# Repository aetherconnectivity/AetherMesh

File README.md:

# AetherMesh
Design resources for the Sub-GHz AetherMesh modules

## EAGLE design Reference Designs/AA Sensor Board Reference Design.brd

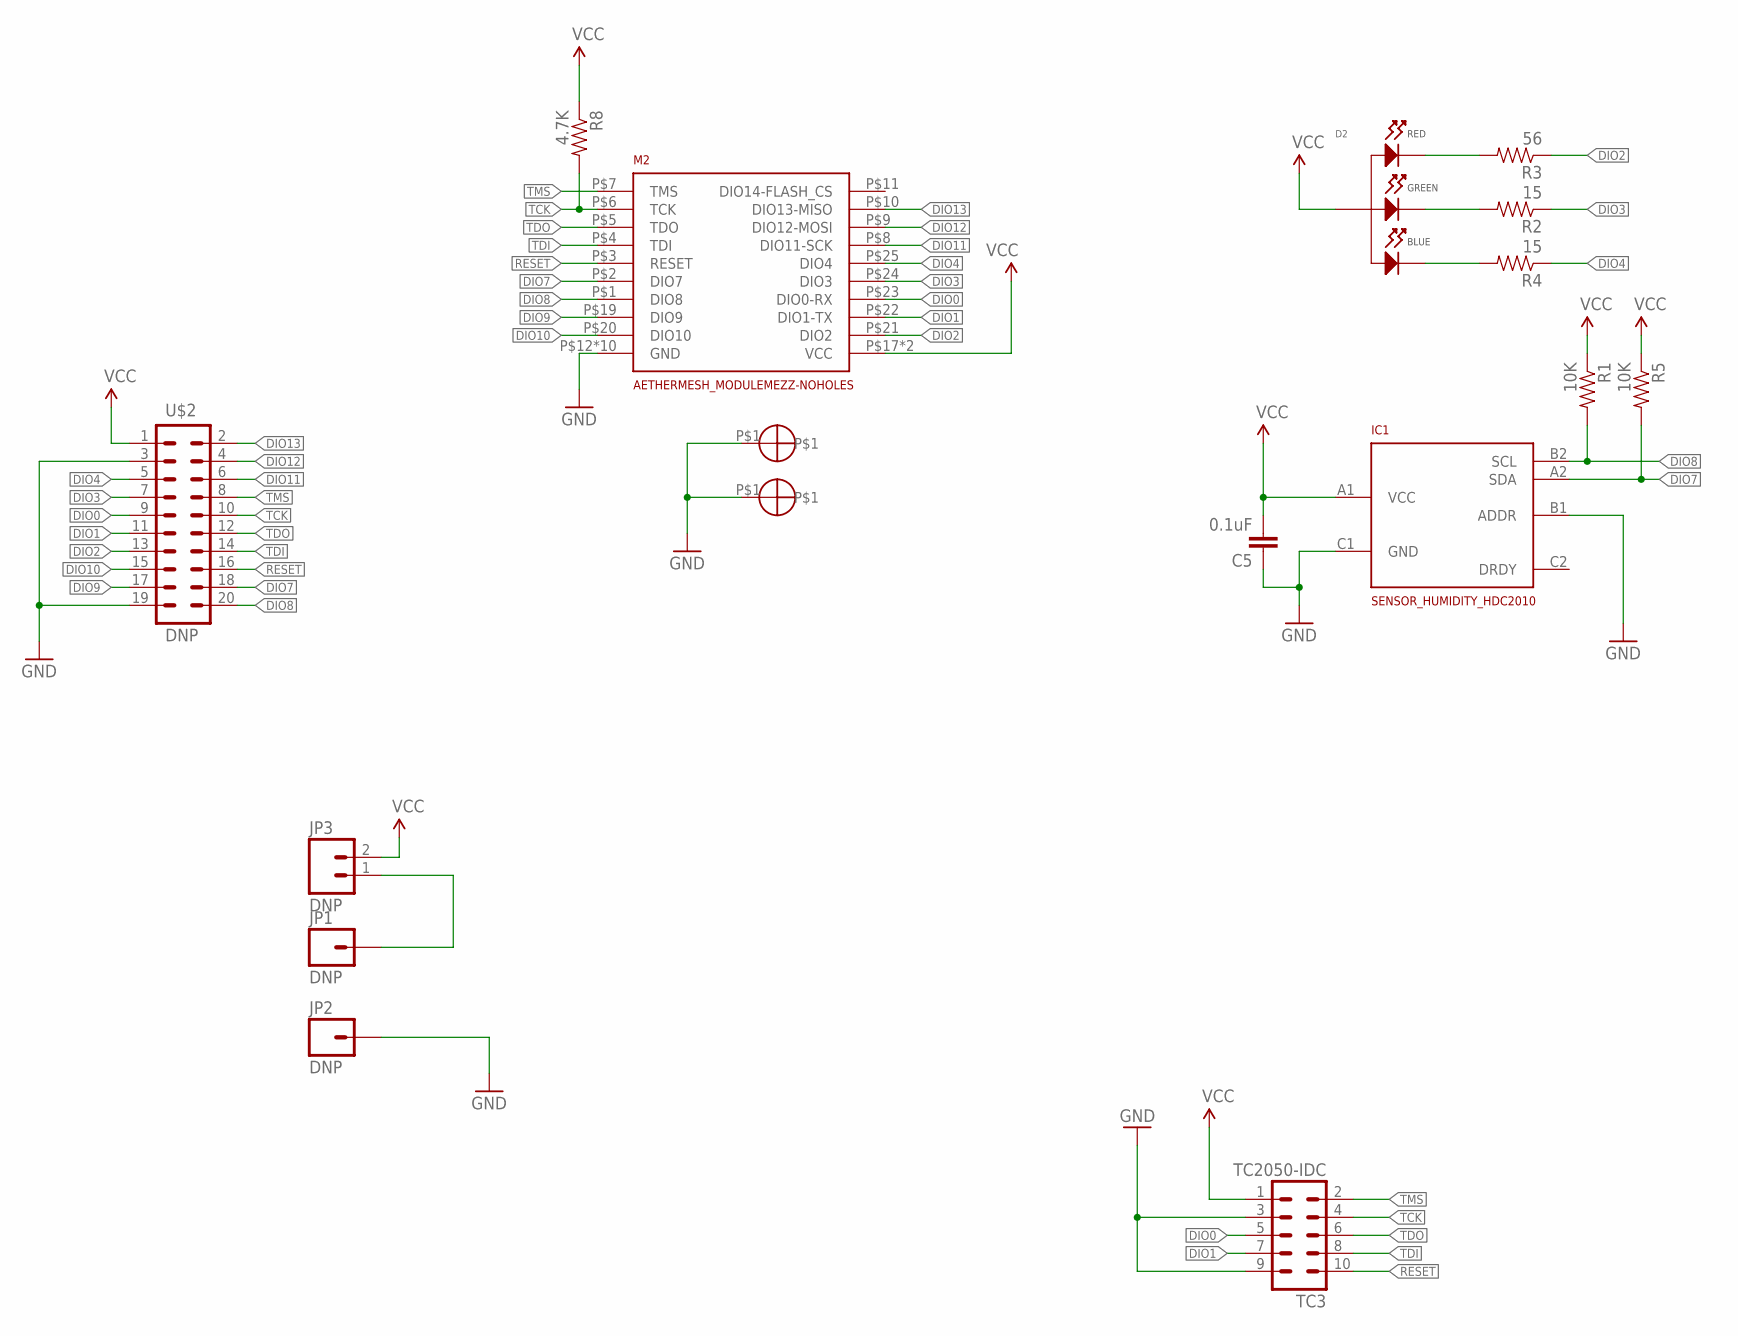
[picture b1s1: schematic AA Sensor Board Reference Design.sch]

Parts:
C5: 0.1uF; C0402; MFG# MF-CAP-0402-0.1uF
D2: LED_RGB_CA_PLCC4; PLCC4; MFG# MF-LED-3228-RGB
IC1: SENSOR_HUMIDITY_HDC2010; HDC2010
JP1, JP2: DNP; 1X01_3.5X.75_BATT_SLOT
JP3: DNP; 1X02_LOCK
M2: AETHERMESH_MODULEMEZZ-NOHOLES; AETHERMESH_MEZZ_MOUNT_NOHOLES
R1, R5: 10K; R0402; MFG# MF-RES-0402-10K
R2, R4: 15; R0402; MFG# RC0402JR-0715RL
R3: 56; R0402; MFG# RC0402JR-0756RL
R8: 4.7K; R0402; MFG# MF-RES-0402-4.7K
S3, S4: STANDOFFWURTH; STANDOFF_WURTH_9774040243R; MFG# 9774040243R
TC3: TC2050-IDC
U$2: DNP; 2X10_LOCK

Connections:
B2: D2.P$2 (CATHODE_RED), R3.P$2 (2)
DIO0: M2.P$23 (DIO0-RX), TC3.5, U$2.9
DIO1: M2.P$22 (DIO1-TX), TC3.7, U$2.11
DIO2: M2.P$21 (DIO2), R3.P$1 (1), U$2.13
DIO3: M2.P$24 (DIO3), R2.P$1 (1), U$2.7
DIO4: M2.P$25 (DIO4), R4.P$1 (1), U$2.5
DIO7: IC1.A2 (SDA), M2.P$2 (DIO7), R5.P$2 (2), U$2.18
DIO8: IC1.B2 (SCL), M2.P$1 (DIO8), R1.P$2 (2), U$2.20
DIO9: M2.P$19 (DIO9), U$2.17
DIO10: M2.P$20 (DIO10), U$2.15
DIO11: M2.P$8 (DIO11-SCK), U$2.6
DIO12: M2.P$9 (DIO12-MOSI), U$2.4
DIO13: M2.P$10 (DIO13-MISO), U$2.2
G2: D2.P$3 (CATHODE_GREEN), R2.P$2 (2)
GND: C5.P$1 (1), IC1.B1 (ADDR), IC1.C1 (GND), JP2.P$1, M2.P$12 (GND), M2.P$13 (GND), M2.P$14 (GND), M2.P$15 (GND), M2.P$16 (GND), M2.P$26 (GND), M2.P$27 (GND), M2.P$28 (GND), M2.P$29 (GND), M2.P$30 (GND), S3.P$1, S4.P$1, TC3.3, TC3.9, U$2.3, U$2.19
unnamed: JP1.P$1, JP3.1
R2: D2.P$4 (CATHODE_BLUE), R4.P$2 (2)
RESET: M2.P$3 (RESET), TC3.10, U$2.16
TCK: M2.P$6 (TCK), R8.P$2 (2), TC3.4, U$2.10
TDI: M2.P$4 (TDI), TC3.8, U$2.14
TDO: M2.P$5 (TDO), TC3.6, U$2.12
TMS: M2.P$7 (TMS), TC3.2, U$2.8
VCC: C5.P$2 (2), D2.P$1 (ANODE), IC1.A1 (VCC), JP3.2, M2.P$17 (VCC), M2.P$18 (VCC), R1.P$1 (1), R5.P$1 (1), R8.P$1 (1), TC3.1, U$2.1

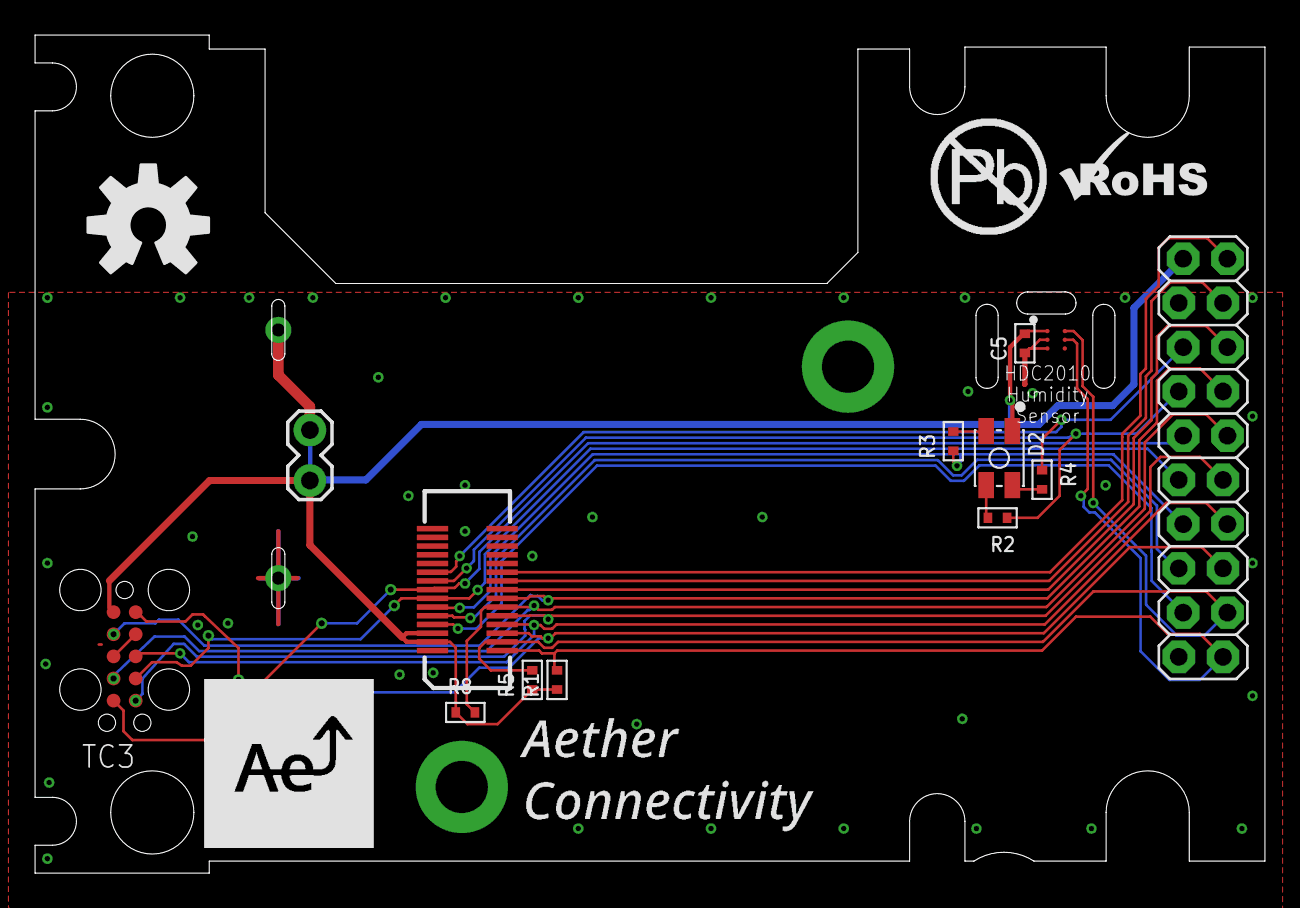
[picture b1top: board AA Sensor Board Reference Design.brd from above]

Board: 4 copper layers, 70.6 x 48.1 mm, 18 parts (0 on the bottom side), 23 nets.

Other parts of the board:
U$3: OSHW-LOGO-L

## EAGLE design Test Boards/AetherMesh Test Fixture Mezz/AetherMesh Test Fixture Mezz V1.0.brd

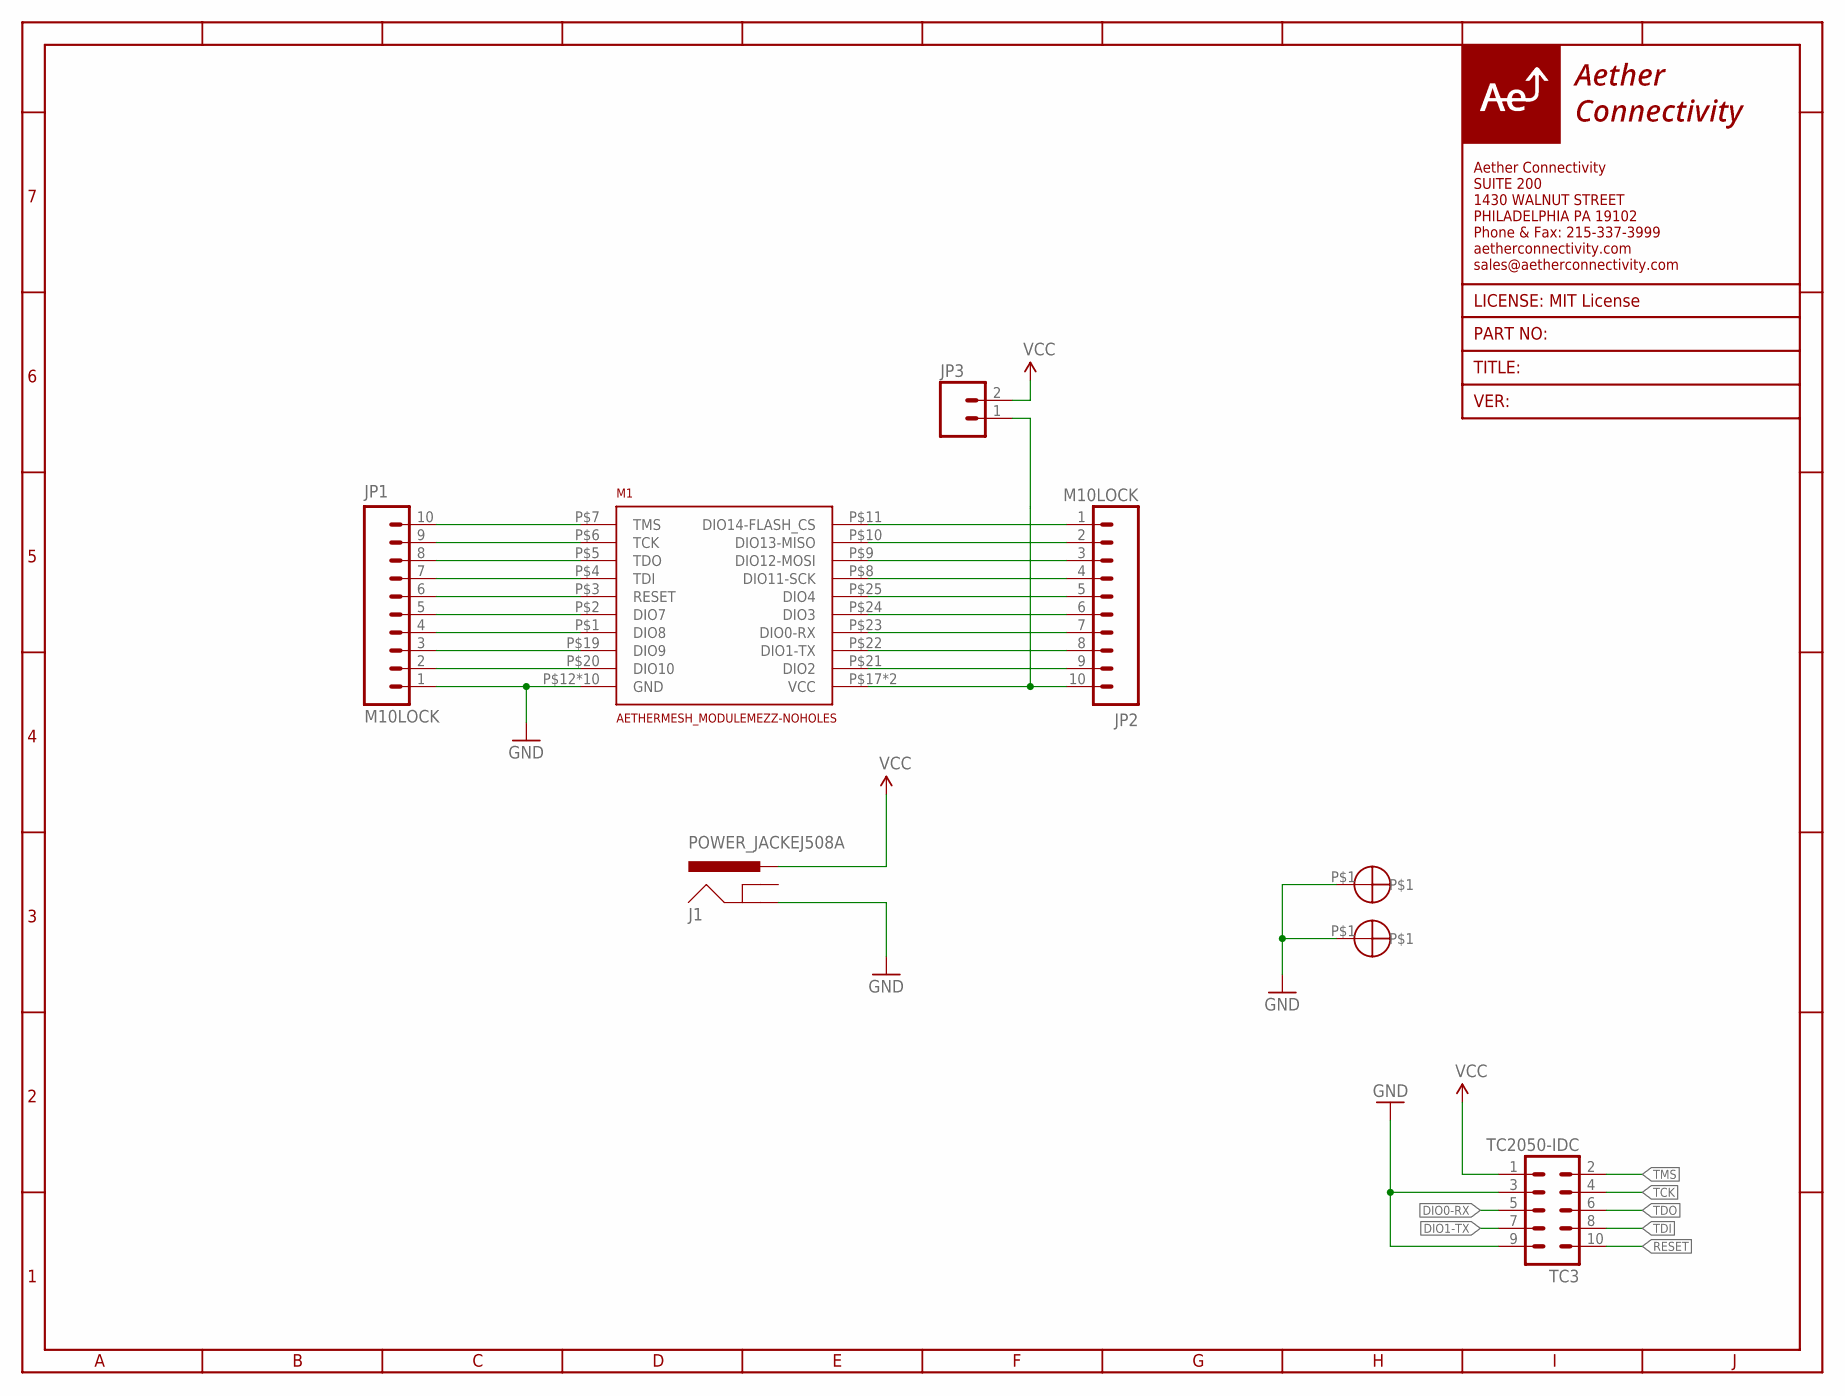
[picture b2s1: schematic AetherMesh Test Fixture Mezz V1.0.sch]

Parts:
J1: POWER_JACKEJ508A; DC_JACK_EJ508A
JP1, JP2: M10LOCK; 1X10_LOCK
JP3: M02LOCK; 1X02_LOCK
M1: AETHERMESH_MODULEMEZZ-NOHOLES; AETHERMESH_MEZZ_MOUNT_NOHOLES
S1, S2: STANDOFFWURTH; STANDOFF_WURTH_9774040243R; MFG# 9774040243R
TC3: TC2050-IDC

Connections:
BUTTON: JP1.2, M1.P$20 (DIO10)
CS: JP1.5, M1.P$2 (DIO7)
DIO0-RX: JP2.7, M1.P$23 (DIO0-RX), TC3.5
DIO1-TX: JP2.8, M1.P$22 (DIO1-TX), TC3.7
DIO2: JP2.9, M1.P$21 (DIO2)
DIO3: JP2.6, M1.P$24 (DIO3)
DIO4: JP2.5, M1.P$25 (DIO4)
ENC_RESET: JP1.4, M1.P$1 (DIO8)
GND: J1.1 (GND), JP1.1, M1.P$12 (GND), M1.P$13 (GND), M1.P$14 (GND), M1.P$15 (GND), M1.P$16 (GND), M1.P$26 (GND), M1.P$27 (GND), M1.P$28 (GND), M1.P$29 (GND), M1.P$30 (GND), S1.P$1, S2.P$1, TC3.3, TC3.9
INT: JP1.3, M1.P$19 (DIO9)
MISO: JP2.2, M1.P$10 (DIO13-MISO)
MOSI: JP2.3, M1.P$9 (DIO12-MOSI)
unnamed: JP2.1, M1.P$11 (DIO14-FLASH_CS)
unnamed: JP2.10, JP3.1, M1.P$17 (VCC), M1.P$18 (VCC)
RESET: JP1.6, M1.P$3 (RESET), TC3.10
SCK: JP2.4, M1.P$8 (DIO11-SCK)
TCK: JP1.9, M1.P$6 (TCK), TC3.4
TDI: JP1.7, M1.P$4 (TDI), TC3.8
TDO: JP1.8, M1.P$5 (TDO), TC3.6
TMS: JP1.10, M1.P$7 (TMS), TC3.2
VCC: J1.3 (PWR), JP3.2, TC3.1

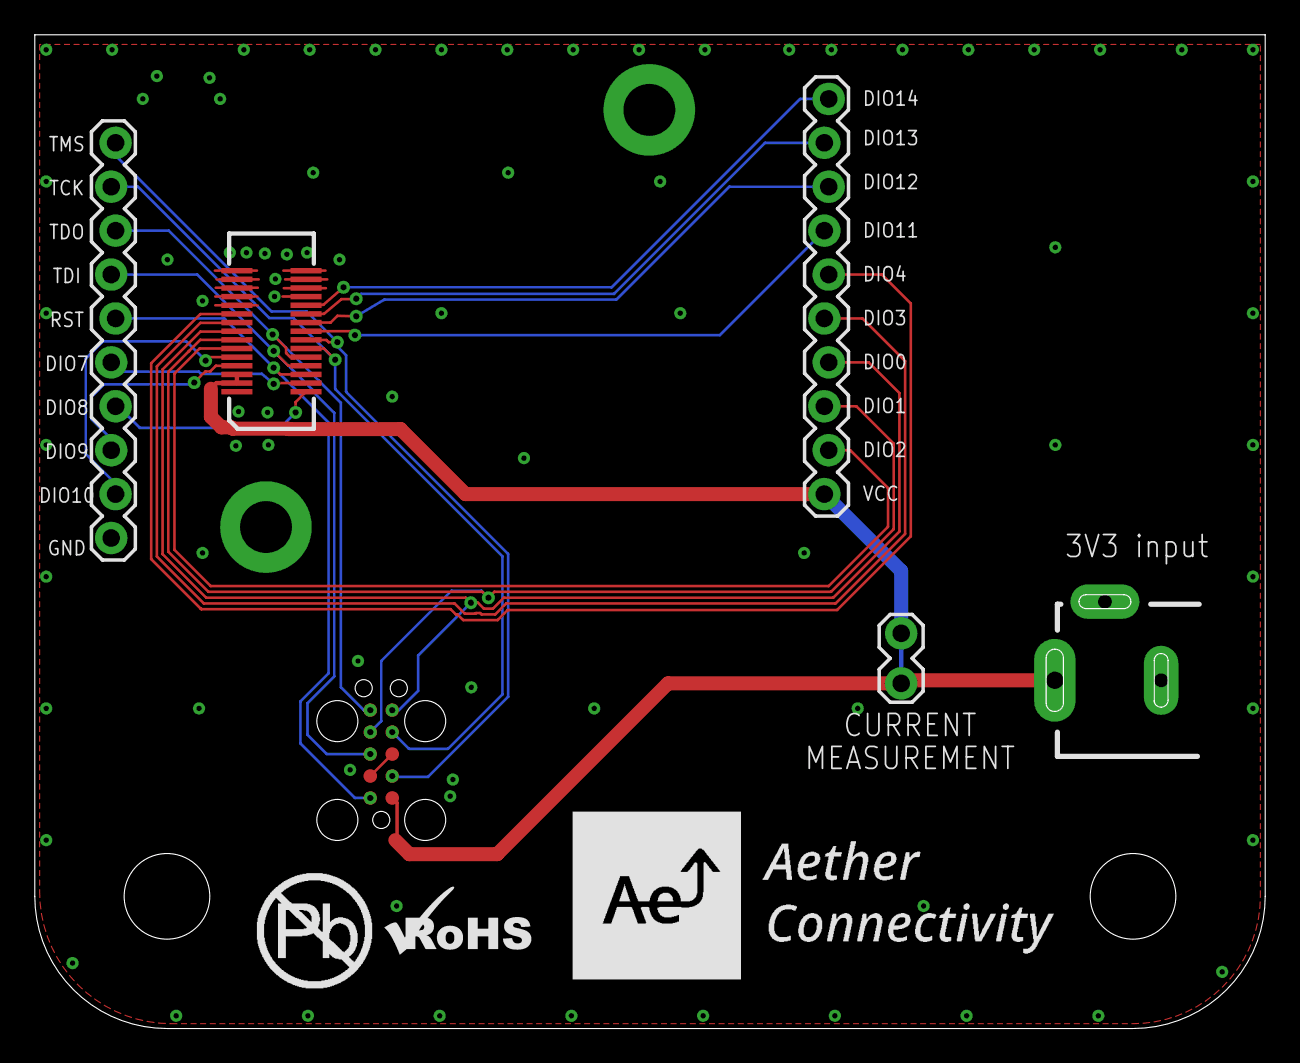
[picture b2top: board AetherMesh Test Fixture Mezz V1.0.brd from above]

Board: 2 copper layers, 71.2 x 57.5 mm, 8 parts (0 on the bottom side), 21 nets.

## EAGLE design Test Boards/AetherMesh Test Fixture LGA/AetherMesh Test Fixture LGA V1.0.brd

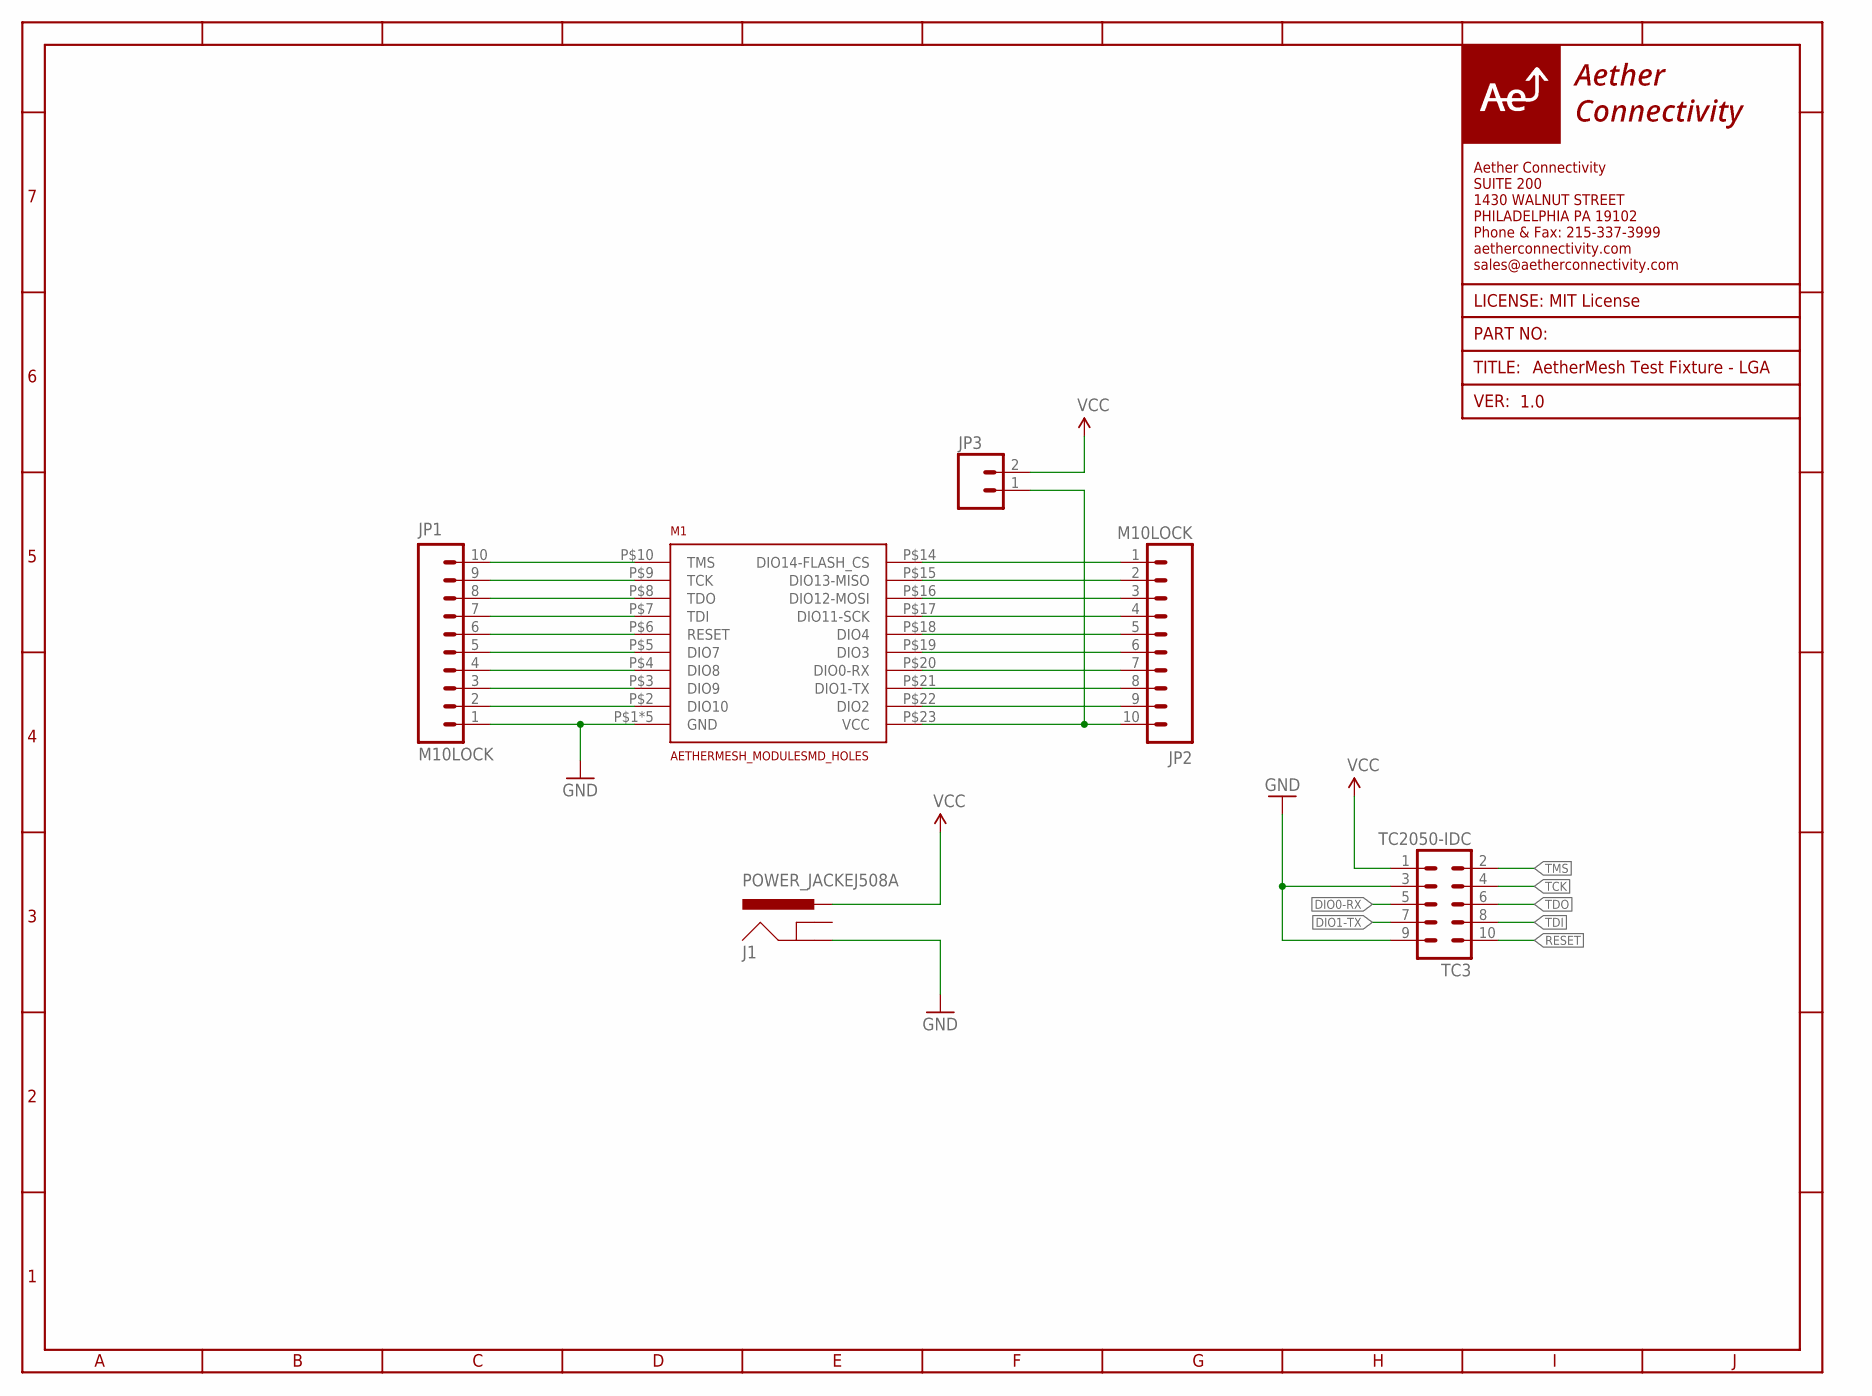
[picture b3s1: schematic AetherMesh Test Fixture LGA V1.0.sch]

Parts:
J1: POWER_JACKEJ508A; DC_JACK_EJ508A
JP1, JP2: M10LOCK; 1X10_LOCK
JP3: M02LOCK; 1X02_LOCK
M1: AETHERMESH_MODULESMD_HOLES; AETHERMESH_SMD_MOUNT_HOLES
TC3: TC2050-IDC

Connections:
BUTTON: JP1.2, M1.P$2 (DIO10)
CS: JP1.5, M1.P$5 (DIO7)
DIO0-RX: JP2.7, M1.P$20 (DIO0-RX), TC3.5
DIO1-TX: JP2.8, M1.P$21 (DIO1-TX), TC3.7
DIO2: JP2.9, M1.P$22 (DIO2)
DIO3: JP2.6, M1.P$19 (DIO3)
DIO4: JP2.5, M1.P$18 (DIO4)
ENC_RESET: JP1.4, M1.P$4 (DIO8)
GND: J1.1 (GND), JP1.1, M1.P$1 (GND), M1.P$11 (GND), M1.P$12 (GND), M1.P$13 (GND), M1.P$24 (GND), TC3.3, TC3.9
INT: JP1.3, M1.P$3 (DIO9)
MISO: JP2.2, M1.P$15 (DIO13-MISO)
MOSI: JP2.3, M1.P$16 (DIO12-MOSI)
unnamed: JP2.1, M1.P$14 (DIO14-FLASH_CS)
unnamed: JP2.10, JP3.1, M1.P$23 (VCC)
RESET: JP1.6, M1.P$6 (RESET), TC3.10
SCK: JP2.4, M1.P$17 (DIO11-SCK)
TCK: JP1.9, M1.P$9 (TCK), TC3.4
TDI: JP1.7, M1.P$7 (TDI), TC3.8
TDO: JP1.8, M1.P$8 (TDO), TC3.6
TMS: JP1.10, M1.P$10 (TMS), TC3.2
VCC: J1.3 (PWR), JP3.2, TC3.1

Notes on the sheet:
1.0
AetherMesh Test Fixture - LGA

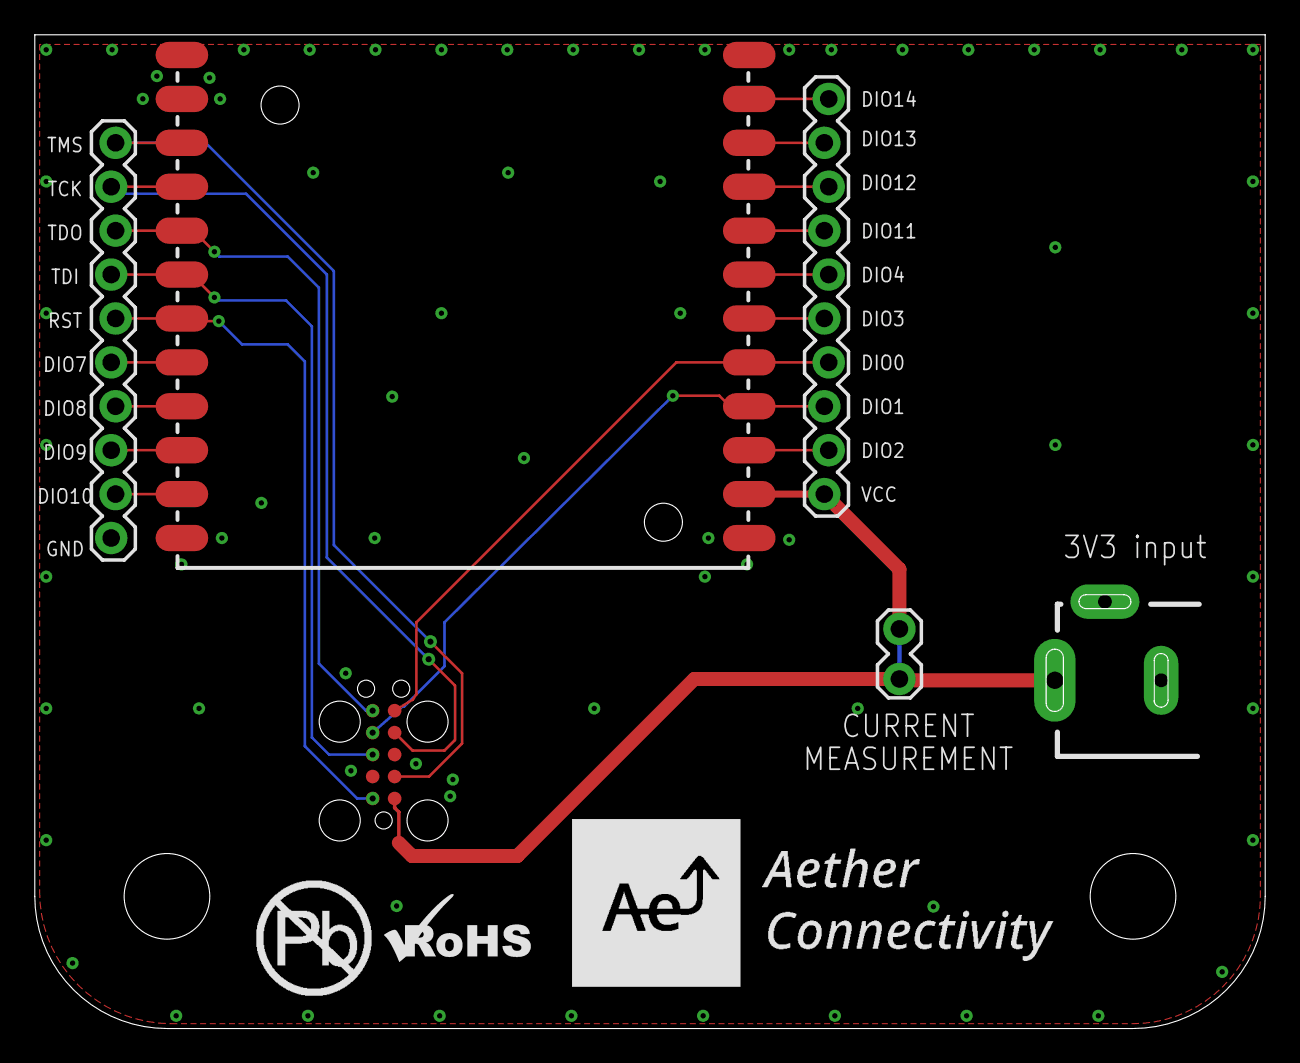
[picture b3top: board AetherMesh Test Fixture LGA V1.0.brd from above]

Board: 2 copper layers, 71.2 x 57.5 mm, 6 parts (0 on the bottom side), 21 nets.

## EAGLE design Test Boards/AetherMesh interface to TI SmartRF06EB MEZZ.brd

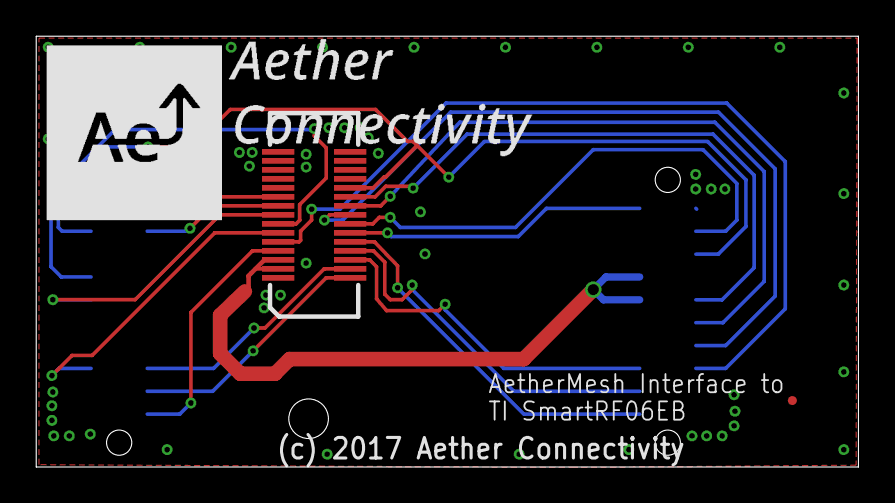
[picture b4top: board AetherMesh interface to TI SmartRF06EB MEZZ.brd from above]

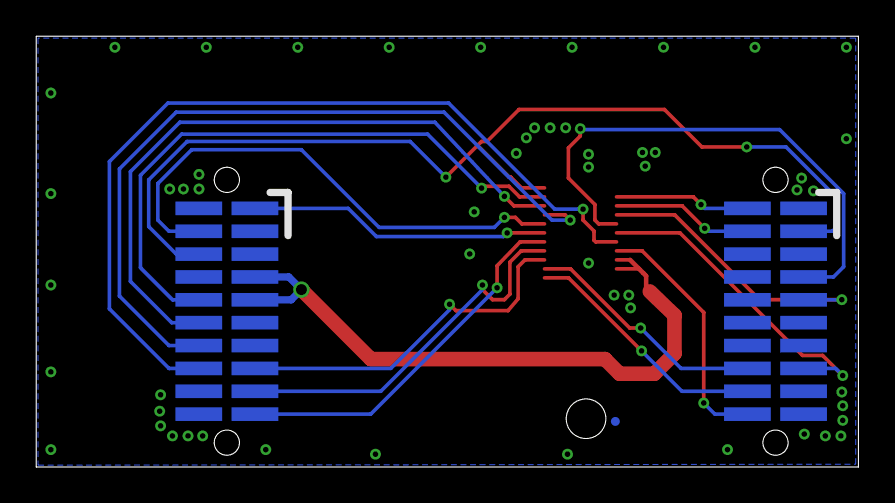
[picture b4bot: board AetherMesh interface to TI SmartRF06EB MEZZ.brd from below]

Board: 4 copper layers, 45.7 x 23.9 mm, 5 parts (3 on the bottom side), 20 nets.

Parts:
FID1, FID2: FIDUCIAL_0.5MM
M1: AETHERMESH_MODULEMEZZ-NOHOLES; AETHERMESH_MEZZ_MOUNT_NOHOLES
P1, P2: M2X10SFM; 2X10_SFM-110-02-S-D-A-K-TR

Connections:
DIO0-RX: M1.P$23, P1.9
DIO1-TX: M1.P$22, P1.7
DIO2: M1.P$21, P1.15
DIO3: M1.P$24, P1.4
DIO4: M1.P$25, P1.2
DIO7: M1.P$2, P1.16
DIO8: M1.P$1, P1.18
DIO9: M1.P$19, P1.20
DIO10: M1.P$20, P2.16
FLASH_CS: M1.P$11, P1.3, P2.6
GND: M1.P$12, M1.P$13, M1.P$14, M1.P$15, M1.P$16, M1.P$26, M1.P$27, M1.P$28, M1.P$29, M1.P$30, P1.1, P1.19, P2.2, P2.20
MISO: M1.P$10, P2.10
MOSI: M1.P$9, P2.12
RESET_N: M1.P$3, P2.15
SCK: M1.P$8, P2.14
TCK: M1.P$6, P2.1
TDI: M1.P$4, P2.17
TDO: M1.P$5, P2.19
TMS: M1.P$7, P2.4
VCC: M1.P$17, M1.P$18, P2.7, P2.9

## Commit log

2017-08-22 Initial commit of AetherMesh test boards
2017-09-11 Re-organized test fixture boards and corrected part number attributes
2017-09-18 Fixed issue with polygons in the stadoff footprints on test boards
2017-11-21 Updated test boards with silkscreen pin names and current measurment jumper
2017-11-21 Added 3D CAD models of AetherMesh module
2017-12-14 Added AA battery sensor reference design
2018-02-23 Updated AA sensor board reference design
2018-02-23 Updated AA Sensor reference design with link to Fusion 360 model
2018-03-29 Final revisions to AA sensor reference design for production V1.0
2018-06-13 Updated reference designs and test boards with latest XDS programmer tag connect header

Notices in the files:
Test Boards/AetherMesh interface to TI SmartRF06EB MEZZ.brd:
(c) 2017 Aether Connectivity
parts and their libraries:
SparkFun-Aesthetics: Licensing: Creative Commons ShareAlike 4.0 International - https://creativecommons.org/licenses/by-sa/4.0
3. growflux: LICENSE: MIT License
